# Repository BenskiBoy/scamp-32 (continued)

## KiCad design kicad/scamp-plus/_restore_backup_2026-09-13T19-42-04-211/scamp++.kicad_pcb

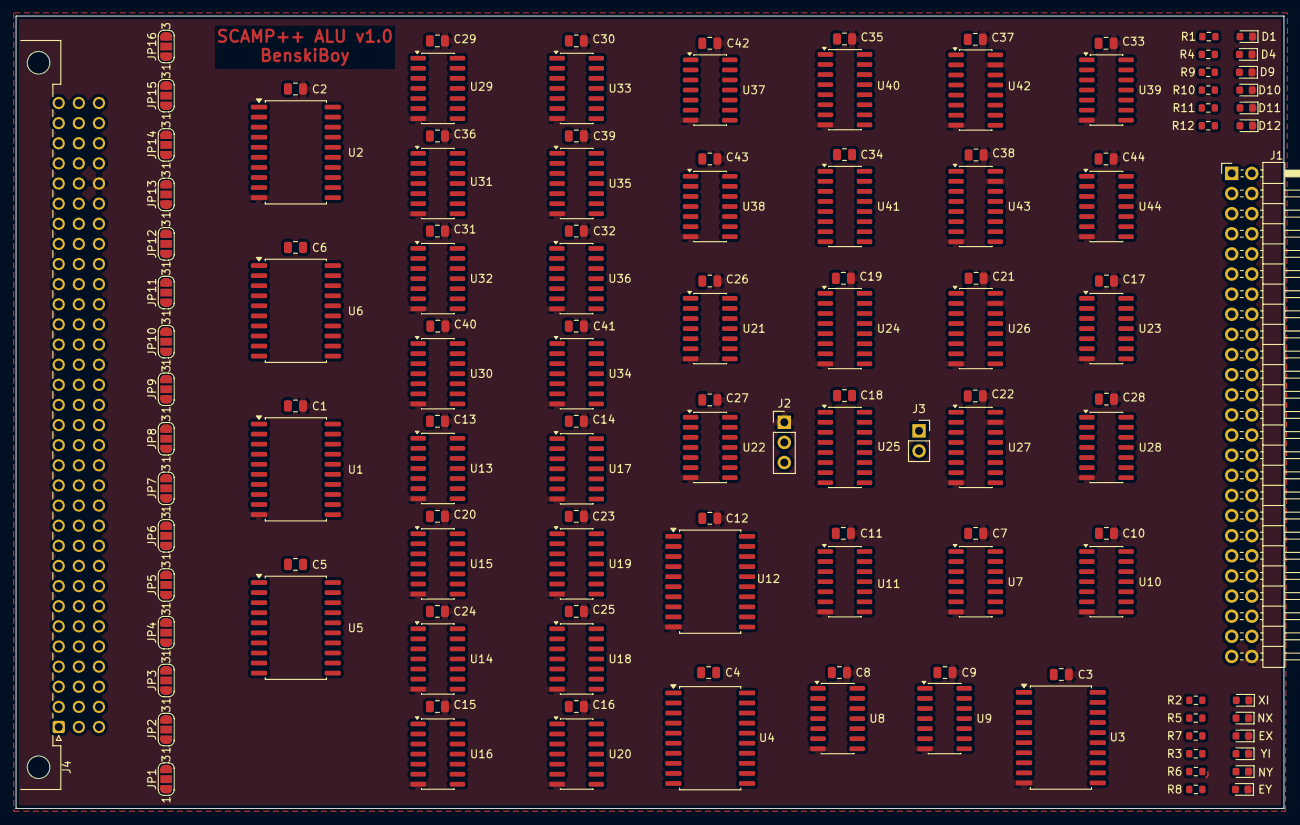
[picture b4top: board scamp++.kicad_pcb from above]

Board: 2 copper layers, 160.0 x 100.0 mm, 132 parts (0 on the bottom side), 264 nets.

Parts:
C1, C2, C3, C4, C5, C6, C7, C8, C9, C10, C11, C12, C13, C14, C15, C16, C17, C18, C19, C20, C21, C22, C23, C24, C25, C26, C27, C28, C29, C30, C31, C32, C33, C34, C35, C36, C37, C38, C39, C40, C41, C42, C43, C44: 100nF; C_0805_2012Metric
D1, D4, D9, D10, D11, D12: LED; LED_0603_1608Metric
EX: LED; LED_0603_1608Metric
EY: LED; LED_0603_1608Metric
J1: Conn_02x25_Top_Bottom; PinHeader_2x25_P2.54mm_Horizontal
J2: Conn_01x03_Pin; PinHeader_1x03_P2.54mm_Vertical
J3: Conn_01x02_Pin; PinSocket_1x02_P2.54mm_Vertical
J4: DIN41612_03x32_C_Split; DIN41612_C_3x32_Male_Horizontal_THT
JP1, JP2, JP3, JP4, JP5, JP6, JP7, JP8, JP9, JP10, JP11, JP12, JP13, JP14, JP15, JP16: SolderJumper_3_Open; SolderJumper-3_P1.3mm_Open_RoundedPad1.0x1.5mm_NumberLabels
NX: LED; LED_0603_1608Metric
NY: LED; LED_0603_1608Metric
R1, R2, R3, R4, R5, R6, R7, R8, R9, R10, R11, R12: 2.2K; R_0603_1608Metric
U1, U2, U5, U6, U12: 74ACT377; SOIC-20W_7.5x12.8mm_P1.27mm
U3, U4: 74ACT244; SOIC-20W_7.5x12.8mm_P1.27mm
U7, U8, U9, U10: 74ACT32; SOIC-14_3.9x8.7mm_P1.27mm
U11: 74ACT02; SOIC-14_3.9x8.7mm_P1.27mm
U13, U14, U15, U16, U21, U22, U29, U30, U31, U32, U37, U38: 74ACT08; SOIC-14_3.9x8.7mm_P1.27mm
U17, U18, U19, U20, U23, U28, U33, U34, U35, U36, U39, U44: 74ACT86; SOIC-14_3.9x8.7mm_P1.27mm
U24, U25, U40, U41: 74ACT283; SOIC-16_3.9x9.9mm_P1.27mm
U26, U27, U42, U43: 74ACT157; SOIC-16_3.9x9.9mm_P1.27mm
XI: LED; LED_0603_1608Metric
YI: LED; LED_0603_1608Metric

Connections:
/ALU_1/C_out: U25.9 (C4), U40.7 (C0)
CLK: J4.c13, U1.11 (CP), U2.11 (CP), U5.11 (CP), U6.11 (CP), U12.11 (CP)
D0: J4.a1, JP1.1 (A)
D0h: JP1.2 (C), U1.3 (D0), U3.18 (O0a), U4.3 (O3b), U5.3 (D0)
D1: J4.a2, JP2.1 (A)
D1h: JP2.2 (C), U1.4 (D1), U3.16 (O1a), U4.5 (O2b), U5.4 (D1)
D2: J4.a3, JP3.1 (A)
D2h: JP3.2 (C), U1.7 (D2), U3.14 (O2a), U4.7 (O1b), U5.7 (D2)
D3: J4.a4, JP4.1 (A)
D3h: JP4.2 (C), U1.8 (D3), U3.12 (O3a), U4.9 (O0b), U5.8 (D3)
D4: J4.a5, JP5.1 (A)
D4h: JP5.2 (C), U1.13 (D4), U3.9 (O0b), U4.12 (O3a), U5.13 (D4)
D5: J4.a6, JP6.1 (A)
D5h: JP6.2 (C), U1.14 (D5), U3.7 (O1b), U4.14 (O2a), U5.14 (D5)
D6: J4.a7, JP7.1 (A)
D6h: JP7.2 (C), U1.17 (D6), U3.5 (O2b), U4.16 (O1a), U5.17 (D6)
D7: J4.a8, JP8.1 (A)
D7h: JP8.2 (C), U1.18 (D7), U3.3 (O3b), U4.18 (O0a), U5.18 (D7)
D8: J4.a9, JP9.1 (A)
D8h: JP9.2 (C), U2.3 (D0), U6.3 (D0)
D9: J4.a10, JP10.1 (A)
D9h: JP10.2 (C), U2.4 (D1), U6.4 (D1)
D10: J4.a11, JP11.1 (A)
D10h: JP11.2 (C), U2.7 (D2), U6.7 (D2)
D11: J4.a12, JP12.1 (A)
D11h: JP12.2 (C), U2.8 (D3), U6.8 (D3)
D12: J4.a13, JP13.1 (A)
D12h: JP13.2 (C), U2.13 (D4), U6.13 (D4)
D13: J4.a14, JP14.1 (A)
D13h: JP14.2 (C), U2.14 (D5), U6.14 (D5)
D14: J4.a15, JP15.1 (A)
D14h: JP15.2 (C), U2.17 (D6), U6.17 (D6)
D15: J4.a16, JP16.1 (A)
D15h: JP16.2 (C), U2.18 (D7), U6.18 (D7)
D16: J4.a17, JP1.3 (B)
D17: J4.a18, JP2.3 (B)
D18: J4.a19, JP3.3 (B)
D19: J4.a20, JP4.3 (B)
D20: J4.a21, JP5.3 (B)
D21: J4.a22, JP6.3 (B)
D22: J4.a23, JP7.3 (B)
D23: J4.a24, JP8.3 (B)
D24: J4.a25, JP9.3 (B)
D25: J4.a26, JP10.3 (B)
D26: J4.a27, JP11.3 (B)
D27: J4.a28, JP12.3 (B)
D28: J4.a29, JP13.3 (B)
D29: J4.a30, JP14.3 (B)
D30: J4.a31, JP15.3 (B)
D31: J4.a32, JP16.3 (B)
E0: J1.17, U3.2 (I0a), U7.1, U23.3
E1: J1.18, U3.4 (I1a), U7.2, U23.6
E2: J1.19, U3.6 (I2a), U7.4, U23.8
E3: J1.20, U3.8 (I3a), U7.5, U23.11
E4: J1.21, U3.11 (I0b), U7.9, U28.3
E5: J1.22, U3.13 (I1b), U7.10, U28.6
E6: J1.23, U3.15 (I2b), U7.12, U28.8
E7: J1.24, U3.17 (I3b), U7.13, U28.11
E8: J1.42, U4.2 (I0a), U8.1, U39.3
E9: J1.43, U4.4 (I1a), U8.2, U39.6
E10: J1.44, U4.6 (I2a), U8.4, U39.8
E11: J1.45, U4.8 (I3a), U8.5, U39.11
E12: J1.46, U4.11 (I0b), U8.9, U44.3
E13: J1.47, U4.13 (I1b), U8.10, U44.6
E14: J1.48, U4.15 (I2b), U8.12, U44.8
E15: J1.49, U4.17 (I3b), U8.13, U12.4 (D1), U44.11
EX: J4.c15, R7.2, U13.2, U13.5, U13.10, U13.13, U15.2, U15.5, U15.10, U15.13, U29.2, U29.5, U29.10, U29.13, U31.2, U31.5, U31.10, U31.13
EY: J4.c17, R8.2, U14.2, U14.5, U14.10, U14.13, U16.2, U16.5, U16.10, U16.13, U30.2, U30.5, U30.10, U30.13, U32.2, U32.5, U32.10, U32.13
F: J4.c19, R12.2, U26.1 (S), U27.1 (S), U42.1 (S), U43.1 (S)
GND: C1.2, C2.2, C3.2, C7.2, C8.2, C9.2, C10.2, C11.2, C12.2, C13.2, C14.2, C15.2, C16.2, C17.2, C19.2, C20.2, C21.2, C22.2, C23.2, C24.2, C25.2, C26.2, C27.2, C28.2, C29.2, C30.2, C31.2, C32.2, C33.2, C35.2, C36.2, C37.2, C38.2, C39.2, C40.2, C41.2, C42.2, C43.2, C44.2, D1.1 (K), D4.1 (K), D9.1 (K), D10.1 (K), D11.1 (K), D12.1 (K), EX.1 (K), EY.1 (K), J1.50, J2.1, J4.c28, NX.1 (K), NY.1 (K), U1.10 (GND), U2.10 (GND), U3.10 (GND), U7.7 (GND), U8.7 (GND), U9.7 (GND), U10.7 (GND), U11.7 (GND), U12.10 (GND), U13.7 (GND), U14.7 (GND), U15.7 (GND), U16.7 (GND), U17.7 (GND), U18.7 (GND), U19.7 (GND), U20.7 (GND), U21.7 (GND), U22.7 (GND), U23.7 (GND), U24.8 (GND), U26.8 (GND), U26.15 (E), U27.8 (GND), U27.15 (E), U28.7 (GND), U29.7 (GND), U30.7 (GND), U31.7 (GND), U32.7 (GND), U33.7 (GND), U34.7 (GND), U35.7 (GND), U36.7 (GND), U37.7 (GND), U38.7 (GND), U39.7 (GND), U40.8 (GND), U42.8 (GND), U42.15 (E), U43.8 (GND), U43.15 (E), U44.7 (GND), XI.1 (K), YI.1 (K)
LT: J4.c2, R10.2, U12.5 (Q1)
NO: J4.c20, R11.2, U23.2, U23.5, U23.10, U23.13, U28.2, U28.5, U28.10, U28.13, U39.2, U39.5, U39.10, U39.13, U44.2, U44.5, U44.10, U44.13
NX: J4.c16, R5.2, U17.2, U17.5, U17.10, U17.13, U19.2, U19.5, U19.10, U19.13, U33.2, U33.5, U33.10, U33.13, U35.2, U35.5, U35.10, U35.13
NY: J4.c18, R6.2, U18.2, U18.5, U18.10, U18.13, U20.2, U20.5, U20.10, U20.13, U34.2, U34.5, U34.10, U34.13, U36.2, U36.5, U36.10, U36.13
unnamed: D1.2 (A), R1.1
unnamed: R2.1, XI.2 (A)
unnamed: R3.1, YI.2 (A)
unnamed: D4.2 (A), R4.1
unnamed: NX.2 (A), R5.1
unnamed: NY.2 (A), R6.1
unnamed: EX.2 (A), R7.1
unnamed: EY.2 (A), R8.1
unnamed: D9.2 (A), R9.1
unnamed: D10.2 (A), R10.1
unnamed: D11.2 (A), R11.1
unnamed: D12.2 (A), R12.1
unnamed: R2.2, U11.4
unnamed: R3.2, U11.10
unnamed: R4.2, U11.13
unnamed: C4.2, U4.10 (GND)
unnamed: C5.2, U5.10 (GND)
unnamed: C6.2, U6.10 (GND)
unnamed: U7.3, U9.12
unnamed: U7.6, U9.13
unnamed: U7.8, U9.9
unnamed: U7.11, U9.10
unnamed: U8.3, U9.4
unnamed: U8.6, U9.5
unnamed: U8.8, U9.1
unnamed: U8.11, U9.2
unnamed: U9.6, U10.1
unnamed: U9.3, U10.2
unnamed: U9.11, U10.4
unnamed: U9.8, U10.5
unnamed: U10.6, U10.9
unnamed: U10.3, U10.10
unnamed: U13.3, U17.1
unnamed: U13.6, U17.4
unnamed: U13.8, U17.9
unnamed: U13.11, U17.12
unnamed: U14.3, U18.1
unnamed: U14.6, U18.4
unnamed: U14.8, U18.9
unnamed: U14.11, U18.12
unnamed: U15.3, U19.1
unnamed: U15.6, U19.4
unnamed: U15.8, U19.9
unnamed: U15.11, U19.12
unnamed: U16.3, U20.1
unnamed: U16.6, U20.4
unnamed: U16.8, U20.9
unnamed: U16.11, U20.12
unnamed: U17.3, U21.1, U24.5 (A1)
unnamed: U17.6, U21.4, U24.3 (A2)
unnamed: U17.8, U21.9, U24.14 (A3)
unnamed: U17.11, U21.12, U24.12 (A4)
unnamed: U20.3, U21.2, U24.6 (B1)
unnamed: U20.6, U21.5, U24.2 (B2)
unnamed: U20.8, U21.10, U24.15 (B3)
unnamed: U20.11, U21.13, U24.11 (B4)
unnamed: U24.9 (C4), U25.7 (C0)
unnamed: U24.4 (S1), U26.3 (I1a)
unnamed: U24.1 (S2), U26.6 (I1b)
unnamed: U24.13 (S3), U26.10 (I1c)
unnamed: U24.10 (S4), U26.13 (I1d)
unnamed: U19.3, U22.1, U25.5 (A1)
unnamed: U19.6, U22.4, U25.3 (A2)
unnamed: U19.8, U22.9, U25.14 (A3)
unnamed: U19.11, U22.12, U25.12 (A4)
unnamed: U18.3, U22.2, U25.6 (B1)
unnamed: U18.6, U22.5, U25.2 (B2)
unnamed: U18.8, U22.10, U25.15 (B3)
unnamed: U18.11, U22.13, U25.11 (B4)
unnamed: C18.2, U25.8 (GND)
unnamed: U25.4 (S1), U27.3 (I1a)
unnamed: U25.1 (S2), U27.6 (I1b)
unnamed: U25.13 (S3), U27.10 (I1c)
unnamed: U25.10 (S4), U27.13 (I1d)
unnamed: U21.3, U26.2 (I0a)
unnamed: U21.6, U26.5 (I0b)
unnamed: U21.8, U26.11 (I0c)
unnamed: U21.11, U26.14 (I0d)
unnamed: U23.1, U26.4 (Za)
unnamed: U23.4, U26.7 (Zb)
unnamed: U23.9, U26.9 (Zc)
unnamed: U23.12, U26.12 (Zd)
unnamed: U22.3, U27.2 (I0a)
unnamed: U22.6, U27.5 (I0b)
unnamed: U22.8, U27.11 (I0c)
unnamed: U22.11, U27.14 (I0d)
unnamed: U27.4 (Za), U28.1
unnamed: U27.7 (Zb), U28.4
unnamed: U27.9 (Zc), U28.9
unnamed: U27.12 (Zd), U28.12
unnamed: U29.3, U33.1
unnamed: U29.6, U33.4
unnamed: U29.8, U33.9
unnamed: U29.11, U33.12
unnamed: U30.3, U34.1
unnamed: U30.6, U34.4
unnamed: U30.8, U34.9
unnamed: U30.11, U34.12
unnamed: U31.3, U35.1
unnamed: U31.6, U35.4
unnamed: U31.8, U35.9
unnamed: U31.11, U35.12
unnamed: U32.3, U36.1
unnamed: U32.6, U36.4
unnamed: U32.8, U36.9
unnamed: U32.11, U36.12
unnamed: U33.3, U37.1, U40.5 (A1)
unnamed: U33.6, U37.4, U40.3 (A2)
unnamed: U33.8, U37.9, U40.14 (A3)
unnamed: U33.11, U37.12, U40.12 (A4)
unnamed: U36.3, U37.2, U40.6 (B1)
unnamed: U36.6, U37.5, U40.2 (B2)
unnamed: U36.8, U37.10, U40.15 (B3)
unnamed: U36.11, U37.13, U40.11 (B4)
unnamed: U40.9 (C4), U41.7 (C0)
unnamed: U40.4 (S1), U42.3 (I1a)
unnamed: U40.1 (S2), U42.6 (I1b)
unnamed: U40.13 (S3), U42.10 (I1c)
unnamed: U40.10 (S4), U42.13 (I1d)
unnamed: U35.3, U38.1, U41.5 (A1)
unnamed: U35.6, U38.4, U41.3 (A2)
unnamed: U35.8, U38.9, U41.14 (A3)
unnamed: U35.11, U38.12, U41.12 (A4)
unnamed: U34.3, U38.2, U41.6 (B1)
unnamed: U34.6, U38.5, U41.2 (B2)
unnamed: U34.8, U38.10, U41.15 (B3)
unnamed: U34.11, U38.13, U41.11 (B4)
unnamed: C34.2, U41.8 (GND)
unnamed: U41.4 (S1), U43.3 (I1a)
unnamed: U41.1 (S2), U43.6 (I1b)
unnamed: U41.13 (S3), U43.10 (I1c)
unnamed: U41.10 (S4), U43.13 (I1d)
unnamed: U37.3, U42.2 (I0a)
unnamed: U37.6, U42.5 (I0b)
unnamed: U37.8, U42.11 (I0c)
unnamed: U37.11, U42.14 (I0d)
unnamed: U39.1, U42.4 (Za)
unnamed: U39.4, U42.7 (Zb)
unnamed: U39.9, U42.9 (Zc)
unnamed: U39.12, U42.12 (Zd)
unnamed: U38.3, U43.2 (I0a)
unnamed: U38.6, U43.5 (I0b)
unnamed: U38.8, U43.11 (I0c)
unnamed: U38.11, U43.14 (I0d)
unnamed: U43.4 (Za), U44.1
unnamed: U43.7 (Zb), U44.4
unnamed: U43.9 (Zc), U44.9
unnamed: U43.12 (Zd), U44.12
VCC: C1.1, C2.1, C3.1, C4.1, C5.1, C6.1, C7.1, C8.1, C9.1, C10.1, C11.1, C12.1, C13.1, C14.1, C15.1, C16.1, C17.1, C18.1, C19.1, C20.1, C21.1, C22.1, C23.1, C24.1, C25.1, C26.1, C27.1, C28.1, C29.1, C30.1, C31.1, C32.1, C33.1, C34.1, C35.1, C36.1, C37.1, C38.1, C39.1, C40.1, C41.1, C42.1, C43.1, C44.1, J1.25, J4.c32, R1.2, U1.20 (VCC), U2.20 (VCC), U3.20 (VCC), U4.20 (VCC), U5.20 (VCC), U6.20 (VCC), U7.14 (VCC), U8.14 (VCC), U9.14 (VCC), U10.14 (VCC), U11.14 (VCC), U12.20 (VCC), U13.14 (VCC), U14.14 (VCC), U15.14 (VCC), U16.14 (VCC), U17.14 (VCC), U18.14 (VCC), U19.14 (VCC), U20.14 (VCC), U21.14 (VCC), U22.14 (VCC), U23.14 (VCC), U24.16 (VCC), U25.16 (VCC), U26.16 (VCC), U27.16 (VCC), U28.14 (VCC), U29.14 (VCC), U30.14 (VCC), U31.14 (VCC), U32.14 (VCC), U33.14 (VCC), U34.14 (VCC), U35.14 (VCC), U36.14 (VCC), U37.14 (VCC), U38.14 (VCC), U39.14 (VCC), U40.16 (VCC), U41.16 (VCC), U42.16 (VCC), U43.16 (VCC), U44.14 (VCC)
X0: J1.1, U1.2 (Q0), U13.1
X1: J1.2, U1.5 (Q1), U13.4
X2: J1.3, U1.6 (Q2), U13.9
X3: J1.4, U1.9 (Q3), U13.12
X4: J1.5, U1.12 (Q4), U15.1
X5: J1.6, U1.15 (Q5), U15.4
X6: J1.7, U1.16 (Q6), U15.9
X7: J1.8, U1.19 (Q7), U15.12
X8: J1.9, U2.2 (Q0), U29.1
X9: J1.10, U2.5 (Q1), U29.4
X10: J1.11, U2.6 (Q2), U29.9
X11: J1.12, U2.9 (Q3), U29.12
X12: J1.13, U2.12 (Q4), U31.1
X13: J1.14, U2.15 (Q5), U31.4
X14: J1.15, U2.16 (Q6), U31.9
X15: J1.16, U2.19 (Q7), U31.12
Y0: J1.26, U5.2 (Q0), U16.1
Y1: J1.27, U5.5 (Q1), U16.4
Y2: J1.28, U5.6 (Q2), U16.9
Y3: J1.29, U5.9 (Q3), U16.12
Y4: J1.30, U5.12 (Q4), U14.1
Y5: J1.31, U5.15 (Q5), U14.4
Y6: J1.32, U5.16 (Q6), U14.9
Y7: J1.33, U5.19 (Q7), U14.12
Y8: J1.34, U6.2 (Q0), U32.1
Y9: J1.35, U6.5 (Q1), U32.4
Y10: J1.36, U6.6 (Q2), U32.9
Y11: J1.37, U6.9 (Q3), U32.12
Y12: J1.38, U6.12 (Q4), U30.1
Y13: J1.39, U6.15 (Q5), U30.4
Y14: J1.40, U6.16 (Q6), U30.9
Y15: J1.41, U6.19 (Q7), U30.12
Z: J4.c1, R9.2, U12.2 (Q0)
Z_new: U11.1, U12.3 (D0)
carry_in: J2.2, U24.7 (C0)
carry_out: J3.1, U41.9 (C4)
nz1: J3.2, U10.8, U11.2
nz2: J2.3, U11.3
~EO: J4.c3, U3.1 (OEa), U3.19 (OEb), U4.1 (OEa), U4.19 (OEb), U11.11, U11.12, U12.1 (~E)
~XI: J4.c4, U1.1 (~E), U2.1 (~E), U11.5, U11.6
~YI: J4.c5, U5.1 (~E), U6.1 (~E), U11.8, U11.9
